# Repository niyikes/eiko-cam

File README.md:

> *a camera built with the Orange Pi CM4, with rotary encoders, a TFT screen and 24-LED RGB ring.*

---
## What is this?

Eiko is a handheld camera built from scratch, with the Orange Pi CM4.

It takes photos, has a TFT screen and a 24-LED RGB ring around the lens that you can change colors with a rotary encoder.
|   |   |
|---|---|
||

## features

- live preview on a 2.8" TFT
- full res JPEG capture (using an 8MP IMX219 camera)
- rgb led ring for colorful lighting & flash
- two rotary encoders (one shoots, one controls the leds)
- saves to SD card

## PCB

## Cad

| Case Front | Case Back | Plate |
|---|---|---|
| | | |

## Firmware
You can find the firmware [here](https://github.com/niyikes/eiko-cam/tree/main/firmware)
| Input | Action |
|-------|--------|
| Rotate enc1 | Navigate menu |
| Press enc1 | Shutter/Click picture |
| Press enc2 | Toggle LED ring on/off |
| Rotate enc2 | Change LED color |

### Flash the firmware
Connect the Orange Pi CM4 and run:

```
./setup.sh
sudo python3 eiko.py
```

## BOM
| Component | Qty | Price (INR) | Total (INR) | Total (USD) | Source |
|-----------|-----|-------------|-------------|-------------|--------|
| Orange Pi CM4 | 1 | 6095 | 6095 | 64.50 | [crazypi.com](https://www.crazypi.com/Orange-Pi-Compute-Module-4) |
| TP4056 LiPo Charger | 1 | 184 | 184 | 1.95 | [robu.in](https://robu.in/product/tp4056-3-7v-lithium-battery-charging-module-1a-usb-type-c-port-ph2-0-terminal/) |
| USB-C Receptacle | 1 | 280 | 280 | 2.96 | [robu.in](https://robu.in/product/usb4745-03-a-gct-usb-sealed-connector-top-mount-usb-type-c-usb-3-2-receptacle-24-position/) |
| MT3608 Boost Converter | 1 | 20 | 20 | 0.21 | [robu.in](https://robu.in/product/mt3608-xian-aerosemi-tech-boost-type-adjustable-2a-2v24v-sot-23-6-dc-dc-converters-rohs/) |
| MicroSD Storage Board | 1 | 389 | 389 | 4.12 | [robu.in](https://robu.in/product/waveshare-micro-sdtf-storage-board/) |
| Alps EC11E Rotary Encoder | 2 | 415.24 | 830.48 | 8.79 | [element14.com](https://in.element14.com/alps/ec11e15204a3/encoder-vertical-30-det-15ppr/dp/1520804) |
| IMX219 Camera | 1 | 3659 | 3659 | 38.72 | [robu.in](https://robu.in/product/arducam-8mp-imx219-camera-module-with-fisheye-lens-for-jeson-nano-and-raspberry-pi-compute-module/) |
| WS2812 24-LED Ring | 1 | 131 | 131 | 1.39 | [robu.in](https://robu.in/product/24-bit-ws2812-5050-rgb-led-built-full-color-driving-lights-circular-development-board/) |
| 2.8" SPI TFT | 1 | 869 | 869 | 9.20 | [robu.in](https://robu.in/product/2-8-inch-spi-touch-screen-module-tft-interface-240320/) |
| 100nF Cap | 1 | 4.64 | 4.64 | 0.05 | [robu.in](https://robu.in/product/100nf-400v-dip-polyester-film-capacitor-pitch10mm/) |
| 1.2k Resistor | 2 | 1.18 | 2.36 | 0.02 | [sharvielectronics.com](https://sharvielectronics.com/product/1-2k-ohm-1-2-watt-resistor-5-tolerance/) |
| 10k Resistor | 5 | 0.45 | 2.25 | 0.02 | [sharvielectronics.com](https://sharvielectronics.com/product/10k-ohm-1-4-watt-resistor-5-tolerance/) |
| 100k Resistor | 2 | 0.45 | 0.90 | 0.01 | [sharvielectronics.com](https://sharvielectronics.com/product/100k-ohm-1-4-watt-resistor-5-tolerance/) |
| 13k Resistor | 2 | 1.08 | 2.16 | 0.02 | [robu.in](https://robu.in/product/mf25-13k-multicomp-pro-through-hole-resistor-13-kohm-mf25-series-250-mw/) |
| LiPo Battery | 1 | 329 | 329 | 3.48 | [robu.in](https://robu.in/product/nova-103450-2000mah-3-7v-lipo-battery-pack/) |
| M2.5 Screws | 10 | 1.24 | 12.40 | 0.13 | [onlyscrews.in](https://onlyscrews.in/products/m2-5-x-6mm-phillips-pan-head-ss-304-screw) |
| Heat Set Inserts | 10 | 2.50 | 25.00 | 0.26 | [flyrobo.in](https://www.flyrobo.in/m2.5-x-5mm-brass-heat-set-threaded-round-insert-nut) |
| **TOTAL** | | | | **$135.45** | |

I loved making this project, it was super fun and i learnt a LOT in the process. SUPER HAPPY WITH HOW IT TURNED OUT! :D

<br><br>
-ˋˏ✄┈┈┈┈
made with <3 by nia

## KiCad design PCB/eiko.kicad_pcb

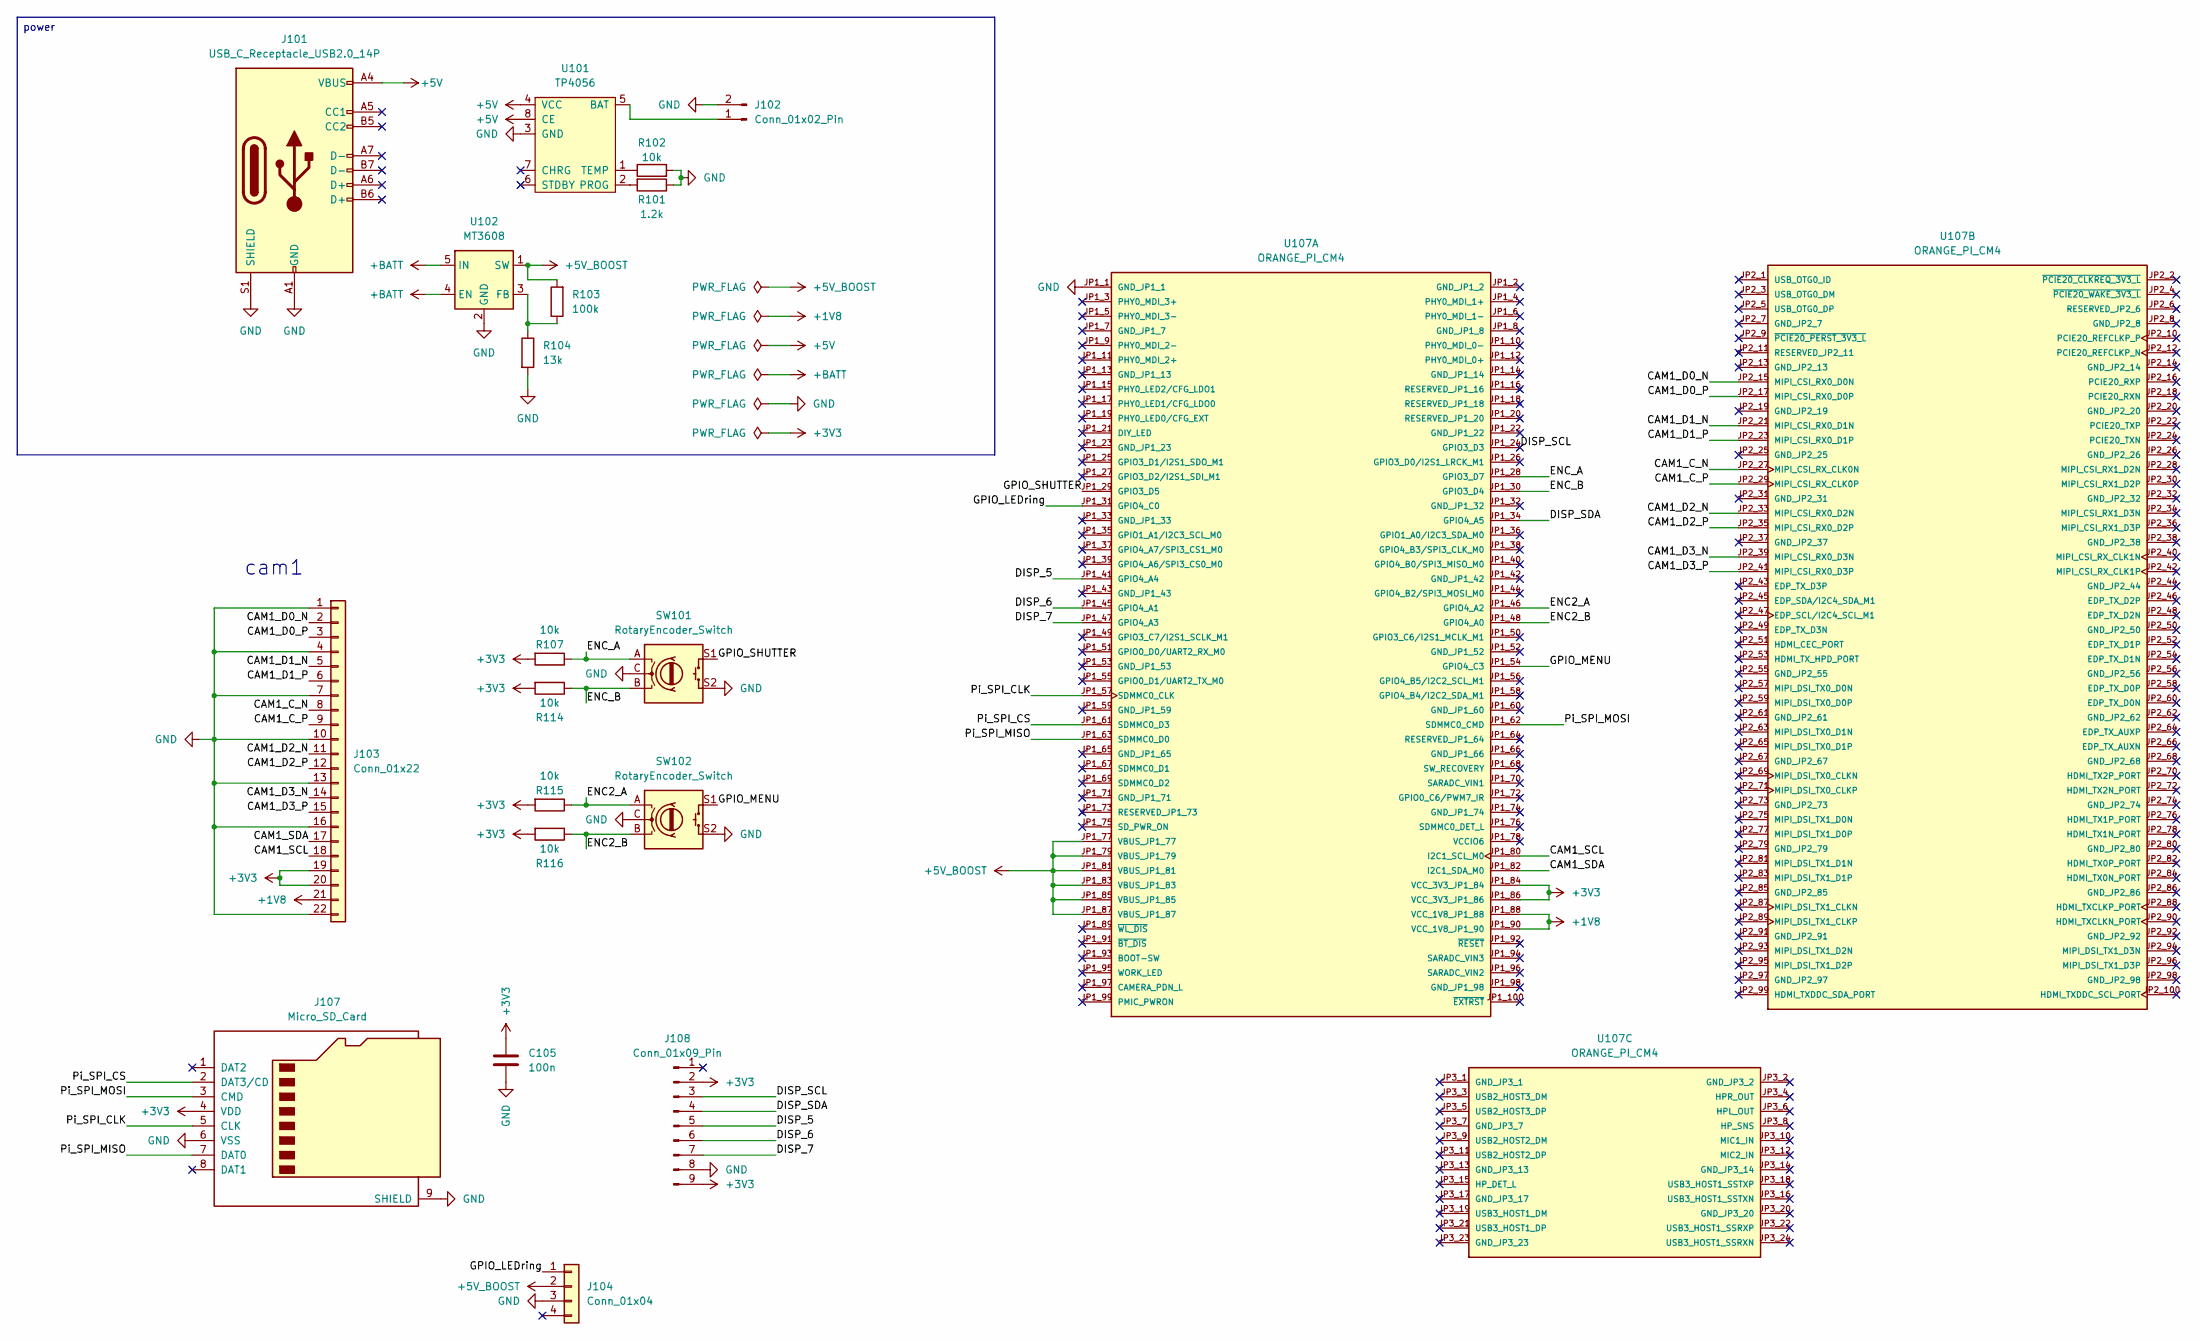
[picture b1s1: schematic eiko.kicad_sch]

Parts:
C105: 100n; C_0603_1608Metric_Pad1.08x0.95mm_HandSolder
J101: USB_C_Receptacle_USB2.0_14P; USB_C_Receptacle_HRO_TYPE-C-31-M-12
J102: Conn_01x02_Pin; JST_PH_B2B-PH-K_1x02_P2.00mm_Vertical
J103: Conn_01x22; Hirose_FH12-22S-0.5SH_1x22-1MP_P0.50mm_Horizontal
J104: Conn_01x04; PinHeader_1x04_P2.54mm_Vertical
J107: Micro_SD_Card; microSD_HC_Wuerth_693072010801
J108: Conn_01x09_Pin; PinHeader_1x09_P2.54mm_Vertical
R101: 1.2k; R_0603_1608Metric_Pad0.98x0.95mm_HandSolder
R102, R107, R114, R115, R116: 10k; R_0603_1608Metric_Pad0.98x0.95mm_HandSolder
R103: 100k; R_0603_1608Metric_Pad0.98x0.95mm_HandSolder
R104: 13k; R_0603_1608Metric_Pad0.98x0.95mm_HandSolder
SW101, SW102: RotaryEncoder_Switch; RotaryEncoder_Alps_EC11E-Switch_Vertical_H20mm
U101: TP4056; SOP-8-1EP_4.57x4.57mm_P1.27mm_EP4.57x4.45mm; LCSC C16581
U102: MT3608; SOT-23-6
U107: ORANGE_PI_CM4; MODULE_ORANGE_PI_CM4; PARTREV v1.2

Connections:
+1V8: J103.21, U107.JP1_88 (VCC_1V8_JP1_88), U107.JP1_90 (VCC_1V8_JP1_90)
+3V3: C105.1, J103.19, J103.20, J107.4 (VDD), J108.2, J108.9, R107.2, R114.2, R115.2, R116.2, U107.JP1_84 (VCC_3V3_JP1_84), U107.JP1_86 (VCC_3V3_JP1_86)
+5V: J101.A4 (VBUS), J101.A9 (VBUS), J101.B4 (VBUS), J101.B9 (VBUS), U101.4 (VCC), U101.8 (CE)
+5V_BOOST: J104.2, R103.2, U102.1 (SW), U107.JP1_77 (VBUS_JP1_77), U107.JP1_79 (VBUS_JP1_79), U107.JP1_81 (VBUS_JP1_81), U107.JP1_83 (VBUS_JP1_83), U107.JP1_85 (VBUS_JP1_85), U107.JP1_87 (VBUS_JP1_87); also elsewhere on the board
+BATT: U102.4 (EN), U102.5 (IN)
/CAM1_C_N: J103.8, U107.JP2_27 (MIPI_CSI_RX_CLK0N)
/CAM1_C_P: J103.9, U107.JP2_29 (MIPI_CSI_RX_CLK0P)
/CAM1_D0_N: J103.2, U107.JP2_15 (MIPI_CSI_RX0_D0N)
/CAM1_D0_P: J103.3, U107.JP2_17 (MIPI_CSI_RX0_D0P)
/CAM1_D1_N: J103.5, U107.JP2_21 (MIPI_CSI_RX0_D1N)
/CAM1_D1_P: J103.6, U107.JP2_23 (MIPI_CSI_RX0_D1P)
/CAM1_D2_N: J103.11, U107.JP2_33 (MIPI_CSI_RX0_D2N)
/CAM1_D2_P: J103.12, U107.JP2_35 (MIPI_CSI_RX0_D2P)
/CAM1_D3_N: J103.14, U107.JP2_39 (MIPI_CSI_RX0_D3N)
/CAM1_D3_P: J103.15, U107.JP2_41 (MIPI_CSI_RX0_D3P)
/CAM1_SCL: J103.18, U107.JP1_80 (I2C1_SCL_M0)
/CAM1_SDA: J103.17, U107.JP1_82 (I2C1_SDA_M0)
/DISP_5: J108.5, U107.JP1_41 (GPIO4_A4)
/DISP_6: J108.6, U107.JP1_45 (GPIO4_A1)
/DISP_7: J108.7, U107.JP1_47 (GPIO4_A3)
/DISP_SCL: J108.3, U107.JP1_24 (GPIO3_D3)
/DISP_SDA: J108.4, U107.JP1_34 (GPIO4_A5)
/ENC2_A: R115.1, SW102.A, U107.JP1_46 (GPIO4_A2)
/ENC2_B: R116.1, SW102.B, U107.JP1_48 (GPIO4_A0)
/ENC_A: R107.1, SW101.A, U107.JP1_28 (GPIO3_D7)
/ENC_B: R114.1, SW101.B, U107.JP1_30 (GPIO3_D4)
/GPIO_LEDring: J104.1, U107.JP1_31 (GPIO4_C0); also elsewhere on the board
/GPIO_MENU: SW102.S1, U107.JP1_54 (GPIO4_C3)
/GPIO_SHUTTER: SW101.S1, U107.JP1_29 (GPIO3_D5)
/Pi_SPI_CLK: J107.5 (CLK), U107.JP1_57 (SDMMC0_CLK)
/Pi_SPI_CS: J107.2 (DAT3/CD), U107.JP1_61 (SDMMC0_D3)
/Pi_SPI_MISO: J107.7 (DAT0), U107.JP1_63 (SDMMC0_D0)
/Pi_SPI_MOSI: J107.3 (CMD), U107.JP1_62 (SDMMC0_CMD)
GND: C105.2, J101.A1 (GND), J101.A12 (GND), J101.B1 (GND), J101.B12 (GND), J101.S1 (SHIELD), J102.2, J103.1, J103.4, J103.7, J103.10, J103.13, J103.16, J103.22, J104.3, J107.6 (VSS), J107.9 (SHIELD), J108.8, R101.1, R102.2, R104.2, SW101.C, SW101.S2, SW102.C, SW102.S2, U101.3 (GND), U102.2 (GND), U107.JP1_1 (GND_JP1_1); also elsewhere on the board
unnamed: J102.1, U101.5 (BAT)
unnamed: R101.2, U101.2 (PROG)
unnamed: R102.1, U101.1 (TEMP)
unnamed: R103.1, R104.1, U102.3 (FB)

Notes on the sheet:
cam1
power

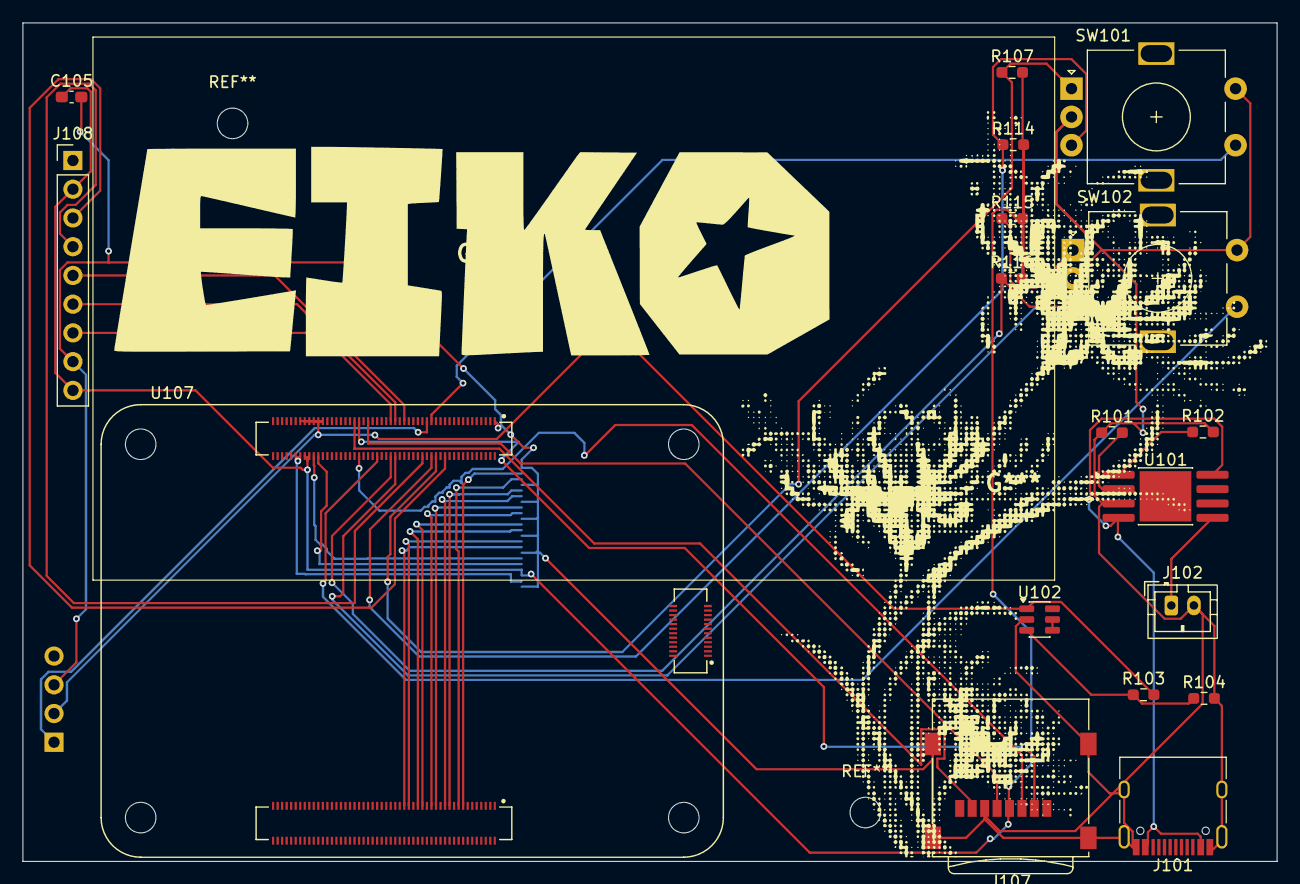
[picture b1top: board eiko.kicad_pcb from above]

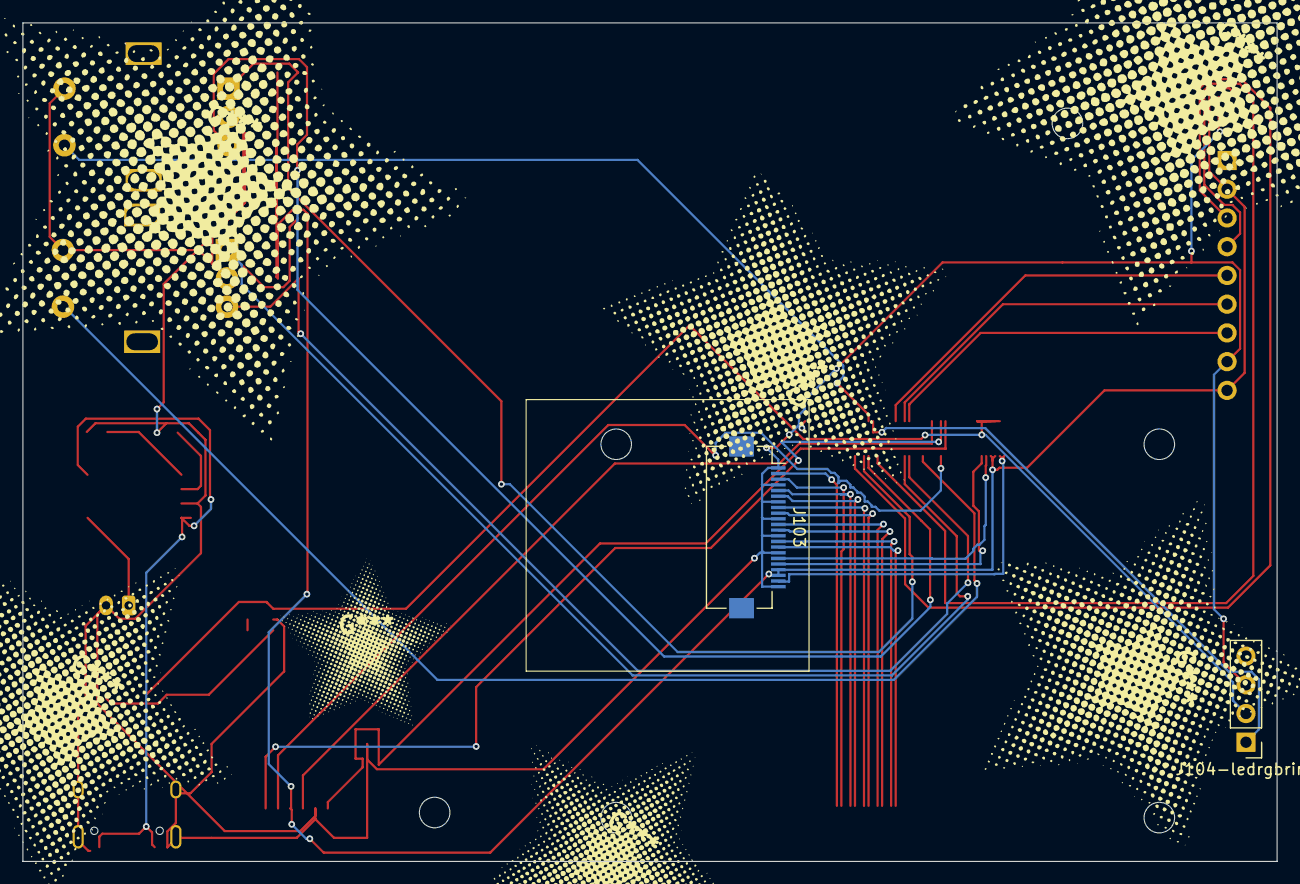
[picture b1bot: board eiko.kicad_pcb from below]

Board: 2 copper layers, 110.8 x 74.1 mm, 20 parts (2 on the bottom side), 38 nets.

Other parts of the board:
J104-ledrgbring: Conn_01x04; PinHeader_1x04_P2.54mm_Vertical

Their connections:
+5V_BOOST: J104-ledrgbring.2; also elsewhere on the board
/GPIO_LEDring: J104-ledrgbring.1; also elsewhere on the board
GND: J104-ledrgbring.3; also elsewhere on the board
